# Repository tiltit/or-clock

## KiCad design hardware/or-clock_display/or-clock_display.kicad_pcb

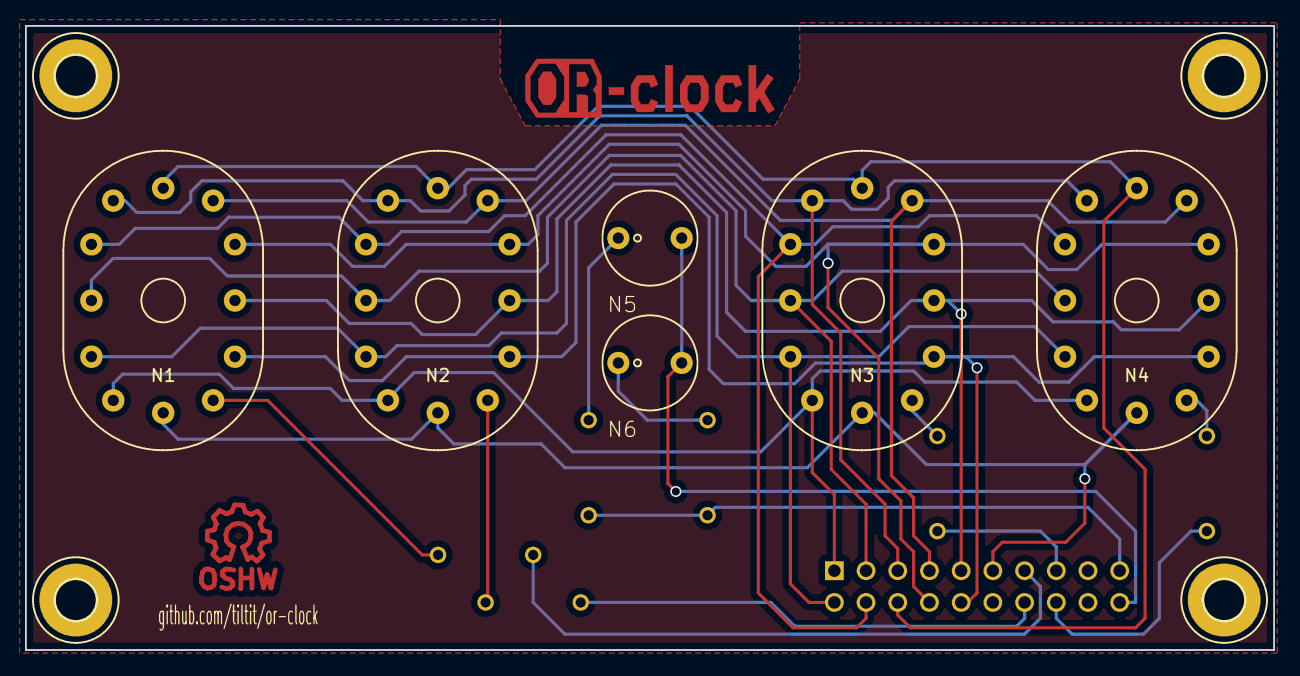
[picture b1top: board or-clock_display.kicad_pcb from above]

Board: 2 copper layers, 100.0 x 50.0 mm, 17 parts (0 on the bottom side), 23 nets.

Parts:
H1, H2, H3, H4: MOUNT-PAD-ROUND3.3; 3,3-PAD
JP1: 2X10
N1, N2, N3, N4: IN-12B; in-12
N5, N6: INS-1
R1, R2, R3, R4: 33K; 0207%2f7
R5, R6: 1M; 0207%2f7

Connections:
/A1: JP1.13, R1.2
/A2: JP1.14, R2.2
/A3: JP1.15, R3.2
/A4: JP1.16, R4.2
/D0: JP1.10, N1.0, N2.0, N3.0, N4.0
/D1: JP1.1, N1.1, N2.1, N3.1, N4.1
/D2: JP1.2, N1.2, N2.2, N3.2, N4.2
/D3: JP1.3, N1.3, N2.3, N3.3, N4.3
/D4: JP1.4, N1.4, N2.4, N3.4, N4.4
/D5: JP1.5, N1.5, N2.5, N3.5, N4.5
/D6: JP1.6, N1.6, N2.6, N3.6, N4.6
/D7: JP1.7, N1.7, N2.7, N3.7, N4.7
/D8: JP1.8, N1.8, N2.8, N3.8, N4.8
/D9: JP1.9, N1.9, N2.9, N3.9, N4.9
/DP: JP1.11, N1.LHDP, N2.LHDP, N3.LHDP, N4.LHDP
/N$1: N1.A, R1.1
/N$2: N2.A, R2.1
/N$3: N3.A, R3.1
/N$4: N4.A, R4.1
/N$5: N5.A, R5.2
/N$6: N6.A, R6.2
/SEP_ANODES: JP1.19, R5.1, R6.1
/SEP_KATHODES: JP1.20, N5.K, N6.K

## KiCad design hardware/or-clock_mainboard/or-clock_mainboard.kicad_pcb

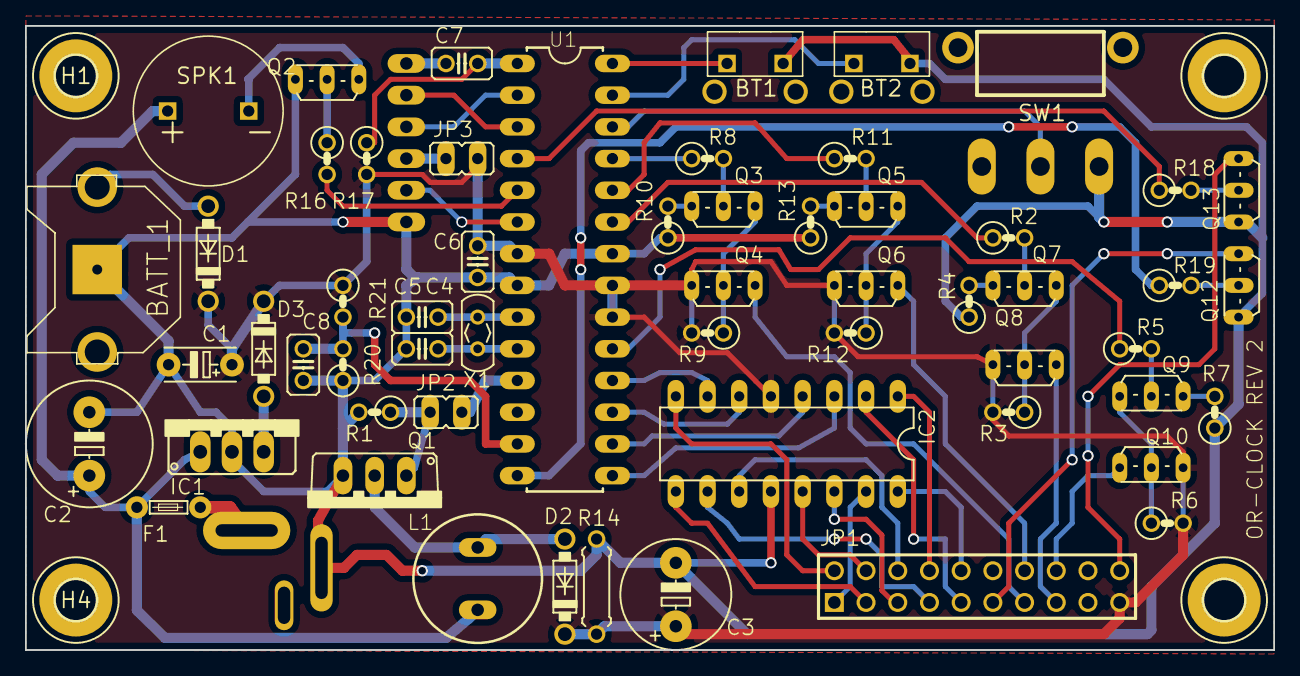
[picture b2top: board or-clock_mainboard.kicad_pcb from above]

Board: 2 copper layers, 100.0 x 50.0 mm, 63 parts (0 on the bottom side), 64 nets.

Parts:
BATT_1: CR1220-THM
BT1, BT2: BUT3305D
C1: 100uf; E5-6
C2: 470uf; E5-10,5
C3: 2.2uf; E5-8,5
C4, C5: 22pf; C025-025X050
C6, C7, C8: 100nf; C025-025X050
D1, D3: 1N5817; DO41-7.6
D2: UF4007; DO41-7.6
F1: LITTLEFUSE
H1, H2, H3, H4: MOUNT-PAD-ROUND3.3; 3,3-PAD
IC1: 78XXS
IC2: 74141N; DIL16
JACK_1: DC_BARREL_PA66_MILL; PA66_DC_JACK_MILL
JP1: 2X10
JP2, JP3: JP1
L1: 100uH; BS11
Q1: IRF740; TO220BV
Q2: BC337; TO92-
Q3, Q5, Q7, Q9, Q12, Q13: MPSA42; TO92-
Q4, Q6, Q8, Q10: MPSA92; TO92-
R1, R2, R5, R8, R11, R17, R18, R19: 10K; 0207%2f2V
R3, R4, R6, R7, R9, R10, R12, R13, R20: 100K; 0207%2f2V
R14: 1M; 0207%2f7
R16: 470R; 0207%2f2V
R21: 270K; 0207%2f2V
SERIAL_CON22: ARDUINO_FTDI_HEADERV; 1X06
SPK1: SUMMER_AL-60P12; AL-60P12_SUMMER
SW1: TS-13P
U1: ATMEGA328P_PDIP; DIL28-3
X1: TC26V

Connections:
+5V: C1.+, C3.+, C6.2, D1.C, D2.C, D3.C, IC2.5, JP1.19, JP3.2, Q4.3, Q6.3, Q8.3, Q10.3, R3.2, R6.2, R9.2, R12.2, R14.2, R17.2, R21.1, U1.7, U1.20, U1.21
+9V: C2.+, F1.2, IC1.IN, L1.1, SPK1.POS
/N$21: Q5.1, Q6.2, R12.1
/N$46: C8.2, R20.2, R21.2, U1.13
A: IC2.3, U1.15
A1: JP1.13, Q4.1
A2: JP1.14, Q6.1
A3: JP1.15, Q8.1
A4: JP1.16, Q10.1
B: IC2.6, U1.17
C: IC2.7, U1.18
D: IC2.4, U1.16
D0: IC2.16, JP1.10
D1: IC2.15, JP1.1
D2: IC2.8, JP1.2
D3: IC2.9, JP1.3
D4: IC2.13, JP1.4
D5: IC2.14, JP1.5
D6: IC2.11, JP1.6
D7: IC2.10, JP1.7
D8: IC2.1, JP1.8
D9: IC2.2, JP1.9
DP: JP1.11, Q12.1
GND: BATT_1.-, BT1.P$2, BT2.P$2, C1.-, C2.-, C3.-, C4.1, C5.1, C6.1, C8.1, IC1.GND, IC2.12, JACK_1.V-, Q1.S, Q2.3, Q12.3, Q13.3, R1.2, R4.1, R7.1, R10.1, R13.1, R14.1, R20.1, SERIAL_CON22.6, SW1.PIN3, U1.8, U1.22
NIX1: R8.1, U1.25
NIX2: R11.1, U1.24
NIX3: R2.1, U1.23
NIX4: R5.1, U1.19
unnamed: BATT_1.+2, D1.A
unnamed: C4.2, U1.10, X1.1
unnamed: C5.2, U1.9, X1.2
unnamed: C7.1, SERIAL_CON22.1
unnamed: D2.A, L1.2, Q1.D
unnamed: D3.A, IC1.OUT
unnamed: F1.1, JACK_1.V+
unnamed: JP2.1, Q1.G, R1.1
unnamed: JP3.1, SERIAL_CON22.4
unnamed: Q2.1, SPK1.NEG
unnamed: Q2.2, R16.1
unnamed: Q3.1, Q4.2, R9.1
unnamed: Q3.2, R8.2
unnamed: Q3.3, R10.2
unnamed: Q5.2, R11.2
unnamed: Q5.3, R13.2
unnamed: Q7.1, Q8.2, R3.1
unnamed: Q7.2, R2.2
unnamed: Q7.3, R4.2
unnamed: Q9.2, R5.2
unnamed: Q9.3, R7.2
unnamed: Q9.1, Q10.2, R6.1
unnamed: Q12.2, R19.2
unnamed: Q13.2, R18.2
OC0B: JP2.2, U1.11
PB0: R19.1, U1.14
PC3: SW1.PIN2, U1.26
PC4: BT2.P$1, U1.27
PC5: BT1.P$1, U1.28
PD2: R18.1, U1.4
PD3: R16.2, U1.5
PD4: SERIAL_CON22.5, U1.6
RESET: C7.2, R17.1, U1.1
RX: SERIAL_CON22.3, U1.2
SEP_KATHODES: JP1.20, Q13.1
TX: SERIAL_CON22.2, U1.3

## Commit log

2015-05-22 rock on
2015-10-25 removed old eagle files
2015-10-25 Added new Kicad files
